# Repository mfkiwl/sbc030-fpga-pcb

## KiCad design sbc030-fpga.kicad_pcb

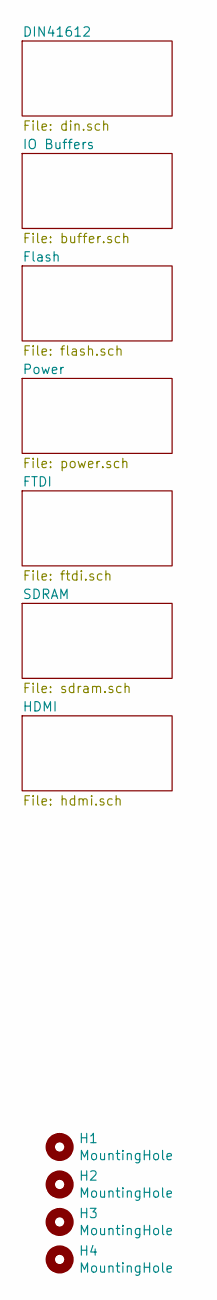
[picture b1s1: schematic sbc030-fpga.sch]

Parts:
H1, H2, H3, H4: MountingHole; MountingHole_3.2mm_M3

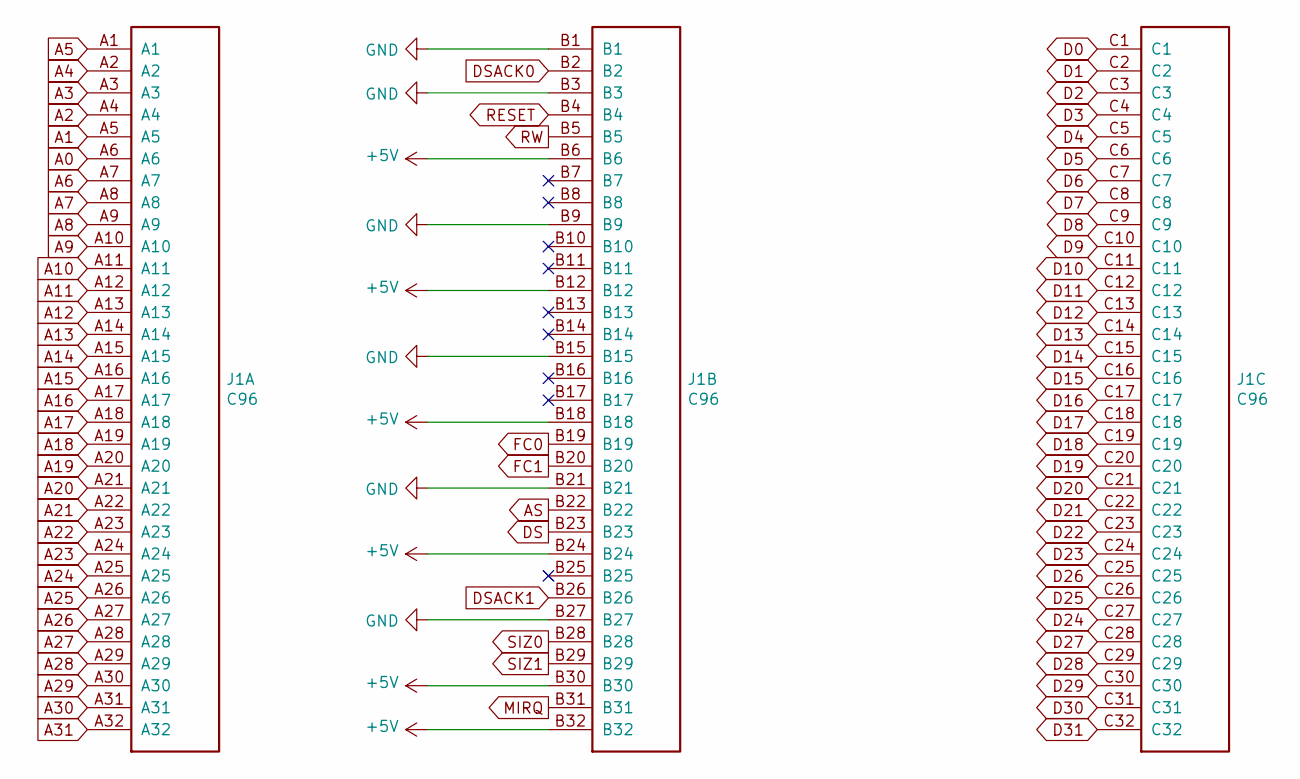
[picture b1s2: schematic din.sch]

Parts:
J1: C96; C96ABCM

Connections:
+5V: J1.B6, J1.B12, J1.B18, J1.B24, J1.B30, J1.B32; also elsewhere on the board
A0: J1.A6; also elsewhere on the board
A1: J1.A5; also elsewhere on the board
A2: J1.A4; also elsewhere on the board
A3: J1.A3; also elsewhere on the board
A4: J1.A2; also elsewhere on the board
A5: J1.A1; also elsewhere on the board
A6: J1.A7; also elsewhere on the board
A7: J1.A8; also elsewhere on the board
A8: J1.A9; also elsewhere on the board
A9: J1.A10; also elsewhere on the board
A10: J1.A11; also elsewhere on the board
A11: J1.A12; also elsewhere on the board
A12: J1.A13; also elsewhere on the board
A13: J1.A14; also elsewhere on the board
A14: J1.A15; also elsewhere on the board
A15: J1.A16; also elsewhere on the board
A16: J1.A17; also elsewhere on the board
A17: J1.A18; also elsewhere on the board
A18: J1.A19; also elsewhere on the board
A19: J1.A20; also elsewhere on the board
A20: J1.A21; also elsewhere on the board
A21: J1.A22; also elsewhere on the board
A22: J1.A23; also elsewhere on the board
A23: J1.A24; also elsewhere on the board
A24: J1.A25; also elsewhere on the board
A25: J1.A26; also elsewhere on the board
A26: J1.A27; also elsewhere on the board
A27: J1.A28; also elsewhere on the board
A28: J1.A29; also elsewhere on the board
A29: J1.A30; also elsewhere on the board
A30: J1.A31; also elsewhere on the board
A31: J1.A32; also elsewhere on the board
AS: J1.B22; also elsewhere on the board
D0: J1.C1; also elsewhere on the board
D1: J1.C2; also elsewhere on the board
D2: J1.C3; also elsewhere on the board
D3: J1.C4; also elsewhere on the board
D4: J1.C5; also elsewhere on the board
D5: J1.C6; also elsewhere on the board
D6: J1.C7; also elsewhere on the board
D7: J1.C8; also elsewhere on the board
D8: J1.C9; also elsewhere on the board
D9: J1.C10; also elsewhere on the board
D10: J1.C11; also elsewhere on the board
D11: J1.C12; also elsewhere on the board
D12: J1.C13; also elsewhere on the board
D13: J1.C14; also elsewhere on the board
D14: J1.C15; also elsewhere on the board
D15: J1.C16; also elsewhere on the board
D16: J1.C17; also elsewhere on the board
D17: J1.C18; also elsewhere on the board
D18: J1.C19; also elsewhere on the board
D19: J1.C20; also elsewhere on the board
D20: J1.C21; also elsewhere on the board
D21: J1.C22; also elsewhere on the board
D22: J1.C23; also elsewhere on the board
D23: J1.C24; also elsewhere on the board
D24: J1.C27; also elsewhere on the board
D25: J1.C26; also elsewhere on the board
D26: J1.C25; also elsewhere on the board
D27: J1.C28; also elsewhere on the board
D28: J1.C29; also elsewhere on the board
D29: J1.C30; also elsewhere on the board
D30: J1.C31; also elsewhere on the board
D31: J1.C32; also elsewhere on the board
DS: J1.B23; also elsewhere on the board
DSACK0: J1.B2; also elsewhere on the board
DSACK1: J1.B26; also elsewhere on the board
FC0: J1.B19; also elsewhere on the board
FC1: J1.B20; also elsewhere on the board
GND: J1.B1, J1.B3, J1.B9, J1.B15, J1.B21, J1.B27; also elsewhere on the board
MIRQ: J1.B31; also elsewhere on the board
RESET: J1.B4; also elsewhere on the board
RW: J1.B5; also elsewhere on the board
SIZ0: J1.B28; also elsewhere on the board
SIZ1: J1.B29; also elsewhere on the board

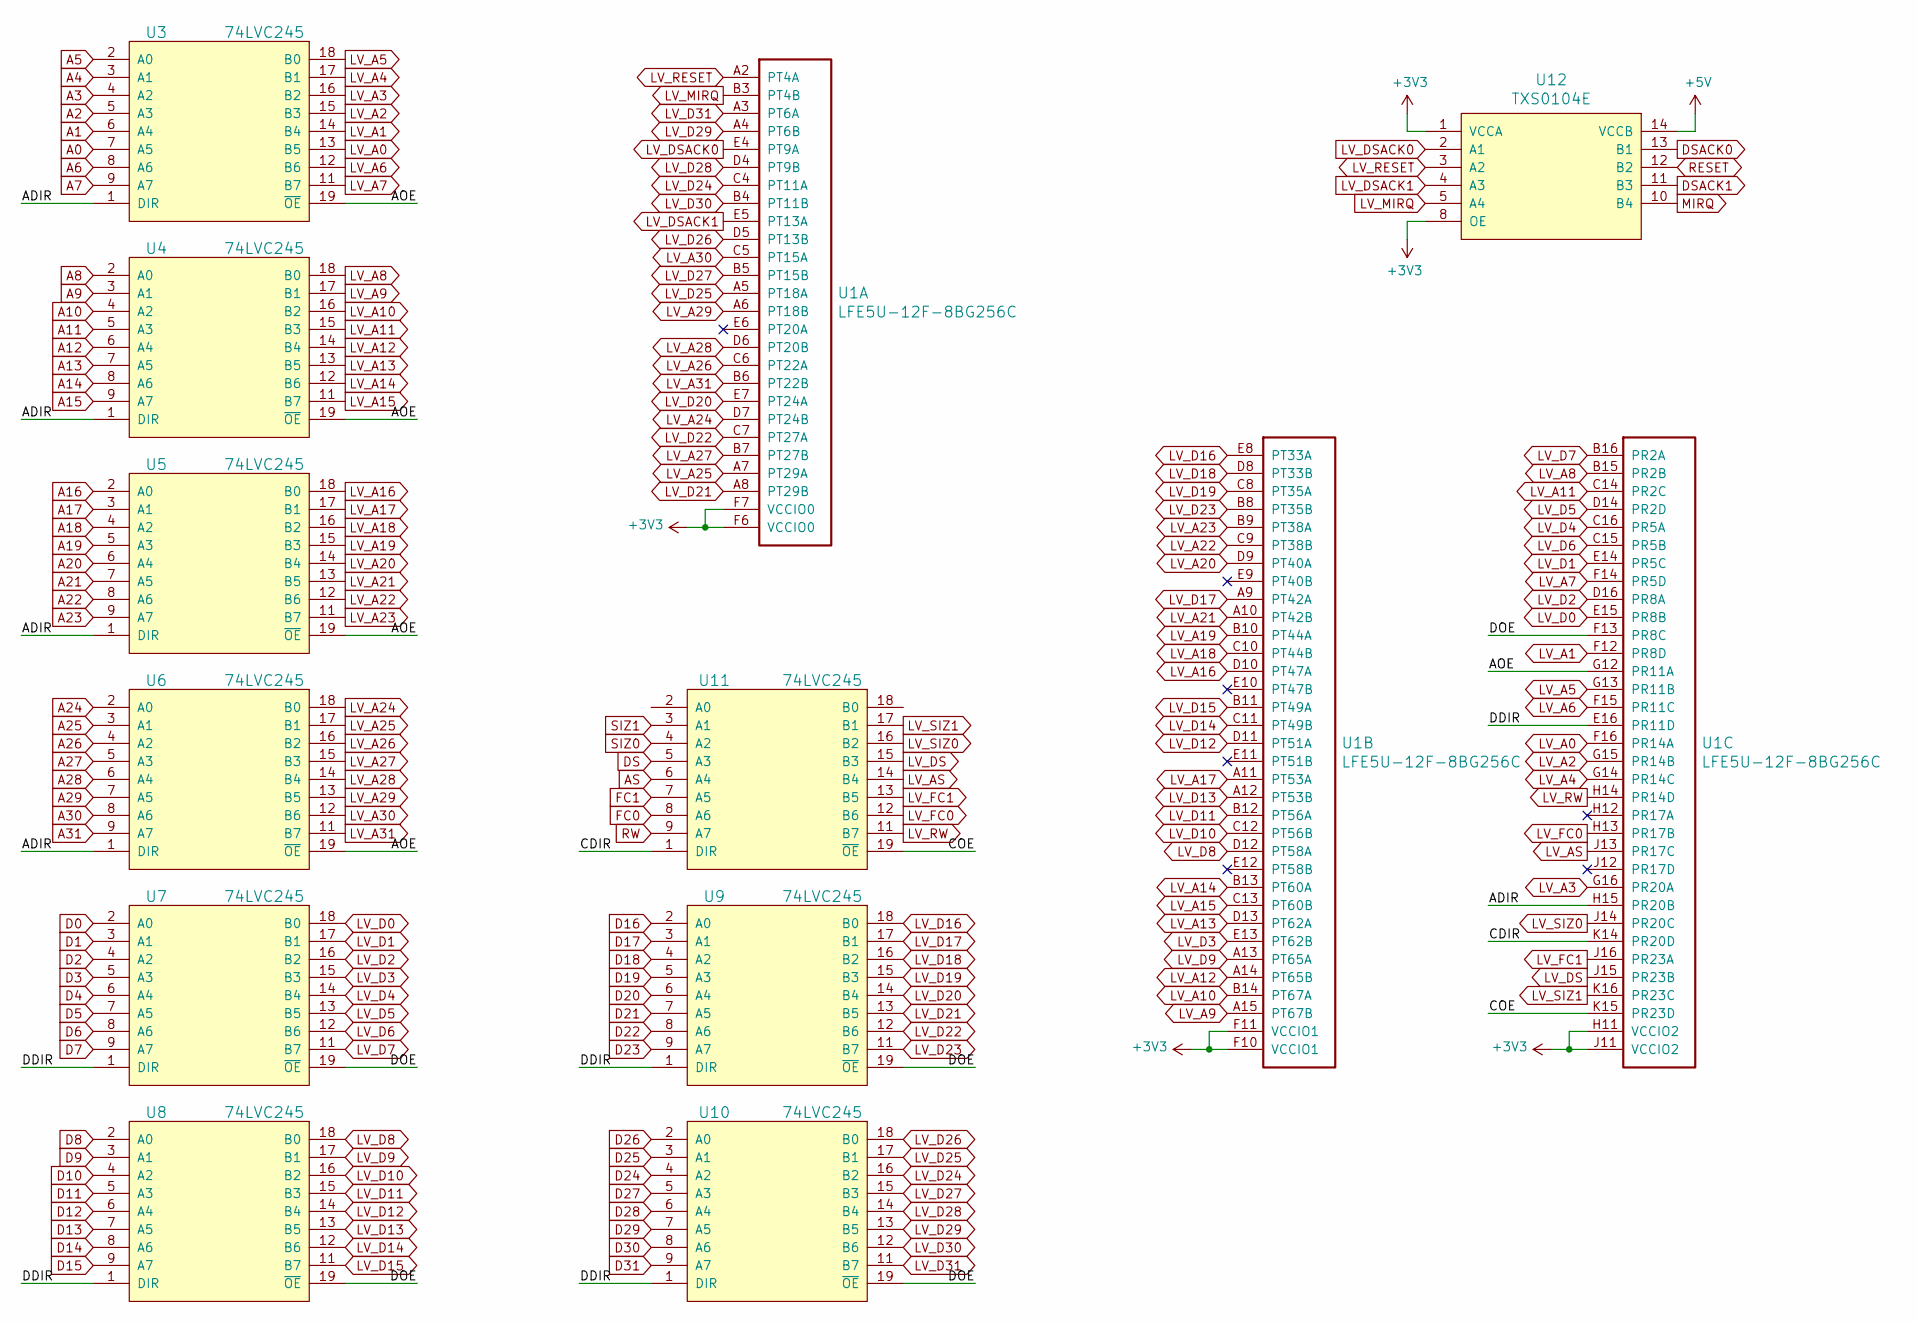
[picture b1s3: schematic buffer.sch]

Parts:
U1: LFE5U-12F-8BG256C; BGA-256_14.0x14.0mm_Layout16x16_P0.8mm_Ball0.45mm_Pad0.32mm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
U3, U4, U5, U6, U7, U8, U9, U10, U11: 74LVC245; TSSOP-20_4.4x6.5mm_P0.65mm
U12: TXS0104E; TSSOP-14_4.4x5mm_P0.65mm

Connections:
+3V3: U1.F6 (VCCIO0), U1.F7 (VCCIO0), U1.F10 (VCCIO1), U1.F11 (VCCIO1), U1.H11 (VCCIO2), U1.J11 (VCCIO2), U3.20 (VCC), U4.20 (VCC), U5.20 (VCC), U6.20 (VCC), U7.20 (VCC), U8.20 (VCC), U9.20 (VCC), U10.20 (VCC), U11.20 (VCC), U12.1 (VCCA), U12.8 (OE); also elsewhere on the board
+5V: U12.14 (VCCB); also elsewhere on the board
/IO Buffers/ADIR: U1.H15 (PR20B), U3.1 (DIR), U4.1 (DIR), U5.1 (DIR), U6.1 (DIR)
/IO Buffers/AOE: U1.G12 (PR11A), U3.19 (~OE), U4.19 (~OE), U5.19 (~OE), U6.19 (~OE)
/IO Buffers/CDIR: U1.K14 (PR20D), U11.1 (DIR)
/IO Buffers/COE: U1.K15 (PR23D), U11.19 (~OE)
/IO Buffers/DDIR: U1.E16 (PR11D), U7.1 (DIR), U8.1 (DIR), U9.1 (DIR), U10.1 (DIR)
/IO Buffers/DOE: U1.F13 (PR8C), U7.19 (~OE), U8.19 (~OE), U9.19 (~OE), U10.19 (~OE)
A0: U3.7 (A5); also elsewhere on the board
A1: U3.6 (A4); also elsewhere on the board
A2: U3.5 (A3); also elsewhere on the board
A3: U3.4 (A2); also elsewhere on the board
A4: U3.3 (A1); also elsewhere on the board
A5: U3.2 (A0); also elsewhere on the board
A6: U3.8 (A6); also elsewhere on the board
A7: U3.9 (A7); also elsewhere on the board
A8: U4.2 (A0); also elsewhere on the board
A9: U4.3 (A1); also elsewhere on the board
A10: U4.4 (A2); also elsewhere on the board
A11: U4.5 (A3); also elsewhere on the board
A12: U4.6 (A4); also elsewhere on the board
A13: U4.7 (A5); also elsewhere on the board
A14: U4.8 (A6); also elsewhere on the board
A15: U4.9 (A7); also elsewhere on the board
A16: U5.2 (A0); also elsewhere on the board
A17: U5.3 (A1); also elsewhere on the board
A18: U5.4 (A2); also elsewhere on the board
A19: U5.5 (A3); also elsewhere on the board
A20: U5.6 (A4); also elsewhere on the board
A21: U5.7 (A5); also elsewhere on the board
A22: U5.8 (A6); also elsewhere on the board
A23: U5.9 (A7); also elsewhere on the board
A24: U6.2 (A0); also elsewhere on the board
A25: U6.3 (A1); also elsewhere on the board
A26: U6.4 (A2); also elsewhere on the board
A27: U6.5 (A3); also elsewhere on the board
A28: U6.6 (A4); also elsewhere on the board
A29: U6.7 (A5); also elsewhere on the board
A30: U6.8 (A6); also elsewhere on the board
A31: U6.9 (A7); also elsewhere on the board
AS: U11.6 (A4); also elsewhere on the board
D0: U7.2 (A0); also elsewhere on the board
D1: U7.3 (A1); also elsewhere on the board
D2: U7.4 (A2); also elsewhere on the board
D3: U7.5 (A3); also elsewhere on the board
D4: U7.6 (A4); also elsewhere on the board
D5: U7.7 (A5); also elsewhere on the board
D6: U7.8 (A6); also elsewhere on the board
D7: U7.9 (A7); also elsewhere on the board
D8: U8.2 (A0); also elsewhere on the board
D9: U8.3 (A1); also elsewhere on the board
D10: U8.4 (A2); also elsewhere on the board
D11: U8.5 (A3); also elsewhere on the board
D12: U8.6 (A4); also elsewhere on the board
D13: U8.7 (A5); also elsewhere on the board
D14: U8.8 (A6); also elsewhere on the board
D15: U8.9 (A7); also elsewhere on the board
D16: U9.2 (A0); also elsewhere on the board
D17: U9.3 (A1); also elsewhere on the board
D18: U9.4 (A2); also elsewhere on the board
D19: U9.5 (A3); also elsewhere on the board
D20: U9.6 (A4); also elsewhere on the board
D21: U9.7 (A5); also elsewhere on the board
D22: U9.8 (A6); also elsewhere on the board
D23: U9.9 (A7); also elsewhere on the board
D24: U10.4 (A2); also elsewhere on the board
D25: U10.3 (A1); also elsewhere on the board
D26: U10.2 (A0); also elsewhere on the board
D27: U10.5 (A3); also elsewhere on the board
D28: U10.6 (A4); also elsewhere on the board
D29: U10.7 (A5); also elsewhere on the board
D30: U10.8 (A6); also elsewhere on the board
D31: U10.9 (A7); also elsewhere on the board
DS: U11.5 (A3); also elsewhere on the board
DSACK0: U12.13 (B1); also elsewhere on the board
DSACK1: U12.11 (B3); also elsewhere on the board
FC0: U11.8 (A6); also elsewhere on the board
FC1: U11.7 (A5); also elsewhere on the board
GND: U3.10 (GND), U4.10 (GND), U5.10 (GND), U6.10 (GND), U7.10 (GND), U8.10 (GND), U9.10 (GND), U10.10 (GND), U11.10 (GND), U12.7 (GND); also elsewhere on the board
LV_A0: U1.F16 (PR14A), U3.13 (B5)
LV_A1: U1.F12 (PR8D), U3.14 (B4)
LV_A2: U1.G15 (PR14B), U3.15 (B3)
LV_A3: U1.G16 (PR20A), U3.16 (B2)
LV_A4: U1.G14 (PR14C), U3.17 (B1)
LV_A5: U1.G13 (PR11B), U3.18 (B0)
LV_A6: U1.F15 (PR11C), U3.12 (B6)
LV_A7: U1.F14 (PR5D), U3.11 (B7)
LV_A8: U1.B15 (PR2B), U4.18 (B0)
LV_A9: U1.A15 (PT67B), U4.17 (B1)
LV_A10: U1.B14 (PT67A), U4.16 (B2)
LV_A11: U1.C14 (PR2C), U4.15 (B3)
LV_A12: U1.A14 (PT65B), U4.14 (B4)
LV_A13: U1.D13 (PT62A), U4.13 (B5)
LV_A14: U1.B13 (PT60A), U4.12 (B6)
LV_A15: U1.C13 (PT60B), U4.11 (B7)
LV_A16: U1.D10 (PT47A), U5.18 (B0)
LV_A17: U1.A11 (PT53A), U5.17 (B1)
LV_A18: U1.C10 (PT44B), U5.16 (B2)
LV_A19: U1.B10 (PT44A), U5.15 (B3)
LV_A20: U1.D9 (PT40A), U5.14 (B4)
LV_A21: U1.A10 (PT42B), U5.13 (B5)
LV_A22: U1.C9 (PT38B), U5.12 (B6)
LV_A23: U1.B9 (PT38A), U5.11 (B7)
LV_A24: U1.D7 (PT24B), U6.18 (B0)
LV_A25: U1.A7 (PT29A), U6.17 (B1)
LV_A26: U1.C6 (PT22A), U6.16 (B2)
LV_A27: U1.B7 (PT27B), U6.15 (B3)
LV_A28: U1.D6 (PT20B), U6.14 (B4)
LV_A29: U1.A6 (PT18B), U6.13 (B5)
LV_A30: U1.C5 (PT15A), U6.12 (B6)
LV_A31: U1.B6 (PT22B), U6.11 (B7)
LV_AS: U1.J13 (PR17C), U11.14 (B4)
LV_D0: U1.E15 (PR8B), U7.18 (B0)
LV_D1: U1.E14 (PR5C), U7.17 (B1)
LV_D2: U1.D16 (PR8A), U7.16 (B2)
LV_D3: U1.E13 (PT62B), U7.15 (B3)
LV_D4: U1.C16 (PR5A), U7.14 (B4)
LV_D5: U1.D14 (PR2D), U7.13 (B5)
LV_D6: U1.C15 (PR5B), U7.12 (B6)
LV_D7: U1.B16 (PR2A), U7.11 (B7)
LV_D8: U1.D12 (PT58A), U8.18 (B0)
LV_D9: U1.A13 (PT65A), U8.17 (B1)
LV_D10: U1.C12 (PT56B), U8.16 (B2)
LV_D11: U1.B12 (PT56A), U8.15 (B3)
LV_D12: U1.D11 (PT51A), U8.14 (B4)
LV_D13: U1.A12 (PT53B), U8.13 (B5)
LV_D14: U1.C11 (PT49B), U8.12 (B6)
LV_D15: U1.B11 (PT49A), U8.11 (B7)
LV_D16: U1.E8 (PT33A), U9.18 (B0)
LV_D17: U1.A9 (PT42A), U9.17 (B1)
LV_D18: U1.D8 (PT33B), U9.16 (B2)
LV_D19: U1.C8 (PT35A), U9.15 (B3)
LV_D20: U1.E7 (PT24A), U9.14 (B4)
LV_D21: U1.A8 (PT29B), U9.13 (B5)
LV_D22: U1.C7 (PT27A), U9.12 (B6)
LV_D23: U1.B8 (PT35B), U9.11 (B7)
LV_D24: U1.C4 (PT11A), U10.16 (B2)
LV_D25: U1.A5 (PT18A), U10.17 (B1)
LV_D26: U1.D5 (PT13B), U10.18 (B0)
LV_D27: U1.B5 (PT15B), U10.15 (B3)
LV_D28: U1.D4 (PT9B), U10.14 (B4)
LV_D29: U1.A4 (PT6B), U10.13 (B5)
LV_D30: U1.B4 (PT11B), U10.12 (B6)
LV_D31: U1.A3 (PT6A), U10.11 (B7)
LV_DS: U1.J15 (PR23B), U11.15 (B3)
LV_DSACK0: U1.E4 (PT9A), U12.2 (A1)
LV_DSACK1: U1.E5 (PT13A), U12.4 (A3)
LV_FC0: U1.H13 (PR17B), U11.12 (B6)
LV_FC1: U1.J16 (PR23A), U11.13 (B5)
LV_MIRQ: U1.B3 (PT4B), U12.5 (A4)
LV_RESET: U1.A2 (PT4A), U12.3 (A2)
LV_RW: U1.H14 (PR14D), U11.11 (B7)
LV_SIZ0: U1.J14 (PR20C), U11.16 (B2)
LV_SIZ1: U1.K16 (PR23C), U11.17 (B1)
MIRQ: U12.10 (B4); also elsewhere on the board
RESET: U12.12 (B2); also elsewhere on the board
RW: U11.9 (A7); also elsewhere on the board
SIZ0: U11.4 (A2); also elsewhere on the board
SIZ1: U11.3 (A1); also elsewhere on the board

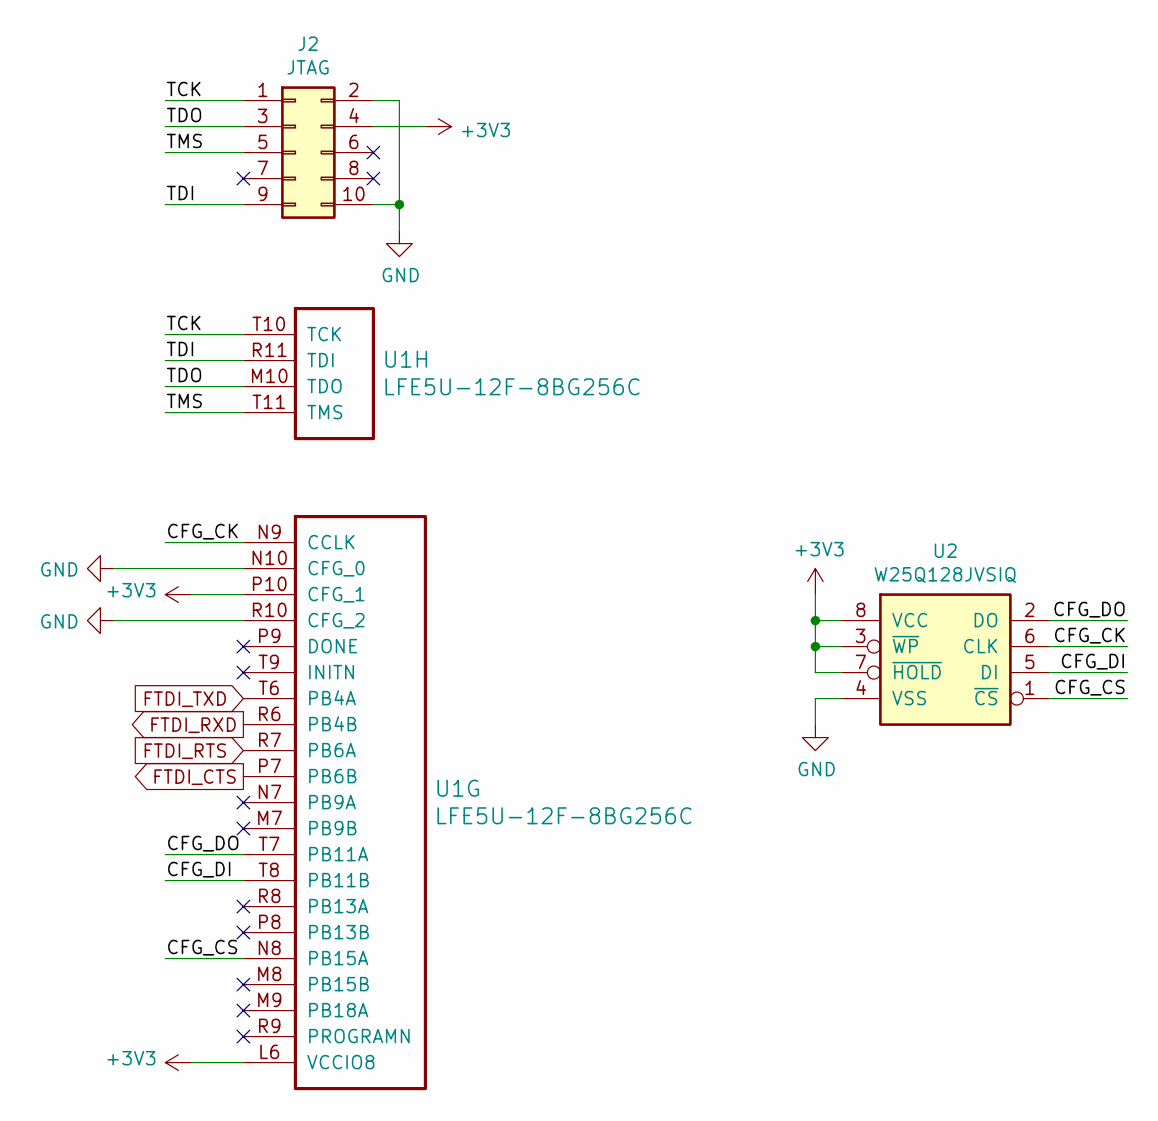
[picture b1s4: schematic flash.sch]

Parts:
J2: JTAG; PinHeader_2x05_P2.54mm_Vertical
U1: LFE5U-12F-8BG256C; BGA-256_14.0x14.0mm_Layout16x16_P0.8mm_Ball0.45mm_Pad0.32mm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
U2: W25Q128JVSIQ; SOIJ-8_5.3x5.3mm_P1.27mm

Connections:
+3V3: J2.4, U1.L6 (VCCIO8), U1.P10 (CFG_1), U2.3 (~WP), U2.7 (~HOLD), U2.8 (VCC); also elsewhere on the board
/Flash/CFG_CK: U1.N9 (CCLK), U2.6 (CLK)
/Flash/CFG_CS: U1.N8 (PB15A), U2.1 (~CS)
/Flash/CFG_DI: U1.T8 (PB11B), U2.5 (DI)
/Flash/CFG_DO: U1.T7 (PB11A), U2.2 (DO)
/Flash/TCK: J2.1, U1.T10 (TCK)
/Flash/TDI: J2.9, U1.R11 (TDI)
/Flash/TDO: J2.3, U1.M10 (TDO)
/Flash/TMS: J2.5, U1.T11 (TMS)
FTDI_CTS: U1.P7 (PB6B); also elsewhere on the board
FTDI_RTS: U1.R7 (PB6A); also elsewhere on the board
FTDI_RXD: U1.R6 (PB4B); also elsewhere on the board
FTDI_TXD: U1.T6 (PB4A); also elsewhere on the board
GND: J2.2, J2.10, U1.N10 (CFG_0), U1.R10 (CFG_2), U2.4 (VSS); also elsewhere on the board

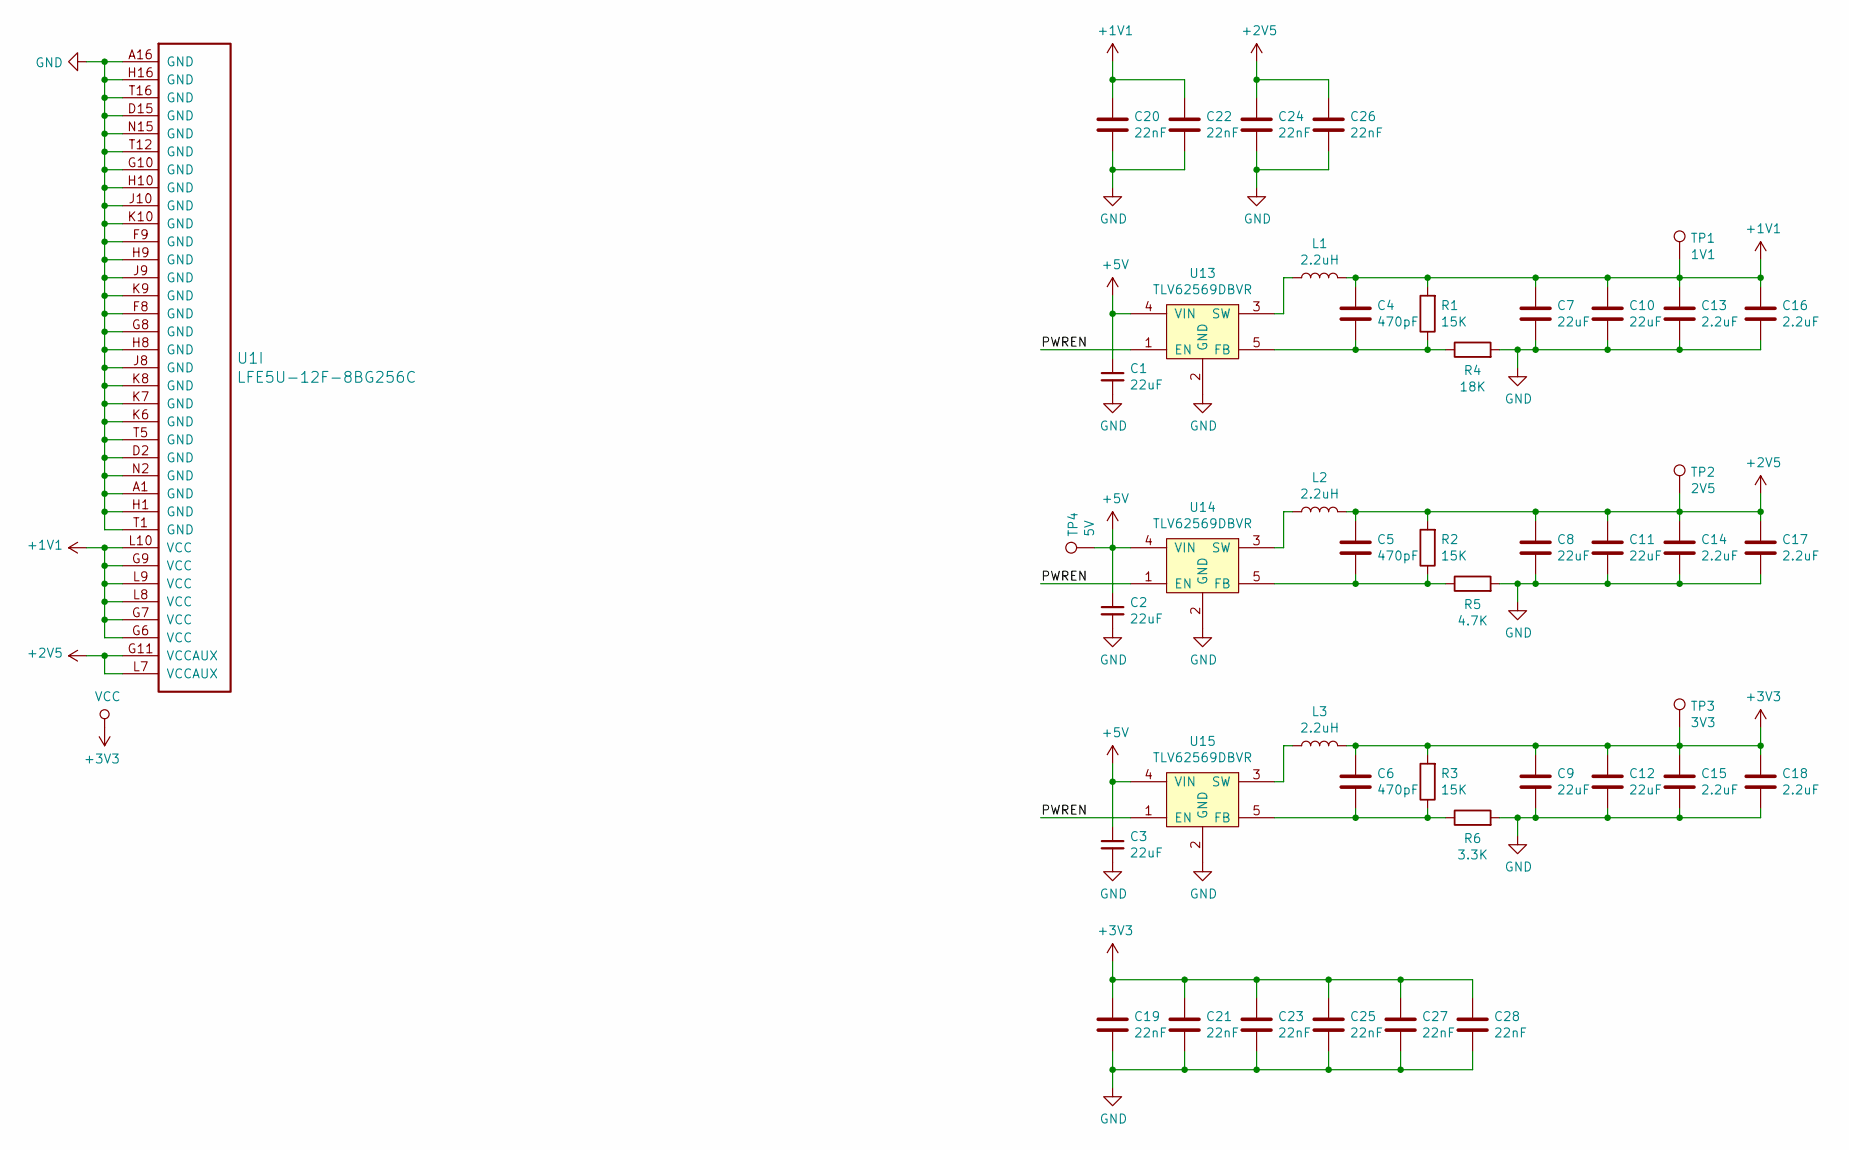
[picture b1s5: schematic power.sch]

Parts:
C1, C2, C3, C7, C8, C9, C10, C11, C12: 22uF; C_0805_2012Metric
C4, C5, C6: 470pF; C_0603_1608Metric
C13, C14, C15, C16, C17, C18: 2.2uF; C_0603_1608Metric
C19, C20, C21, C22, C23, C24, C25, C26, C27, C28: 22nF; C_0402_1005Metric
L1, L2, L3: 2.2uH; L_1210_3225Metric
R1, R2, R3: 15K; R_0603_1608Metric
R4: 18K; R_0603_1608Metric
R5: 4.7K; R_0603_1608Metric
R6: 3.3K; R_0603_1608Metric
TP1: 1V1; TestPoint_Pad_D1.0mm
TP2: 2V5; TestPoint_Pad_D1.0mm
TP3: 3V3; TestPoint_Pad_D1.0mm
TP4: 5V; TestPoint_Pad_D1.0mm
U1: LFE5U-12F-8BG256C; BGA-256_14.0x14.0mm_Layout16x16_P0.8mm_Ball0.45mm_Pad0.32mm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
U13, U14, U15: TLV62569DBVR; SOT-23-5

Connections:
+1V1: C4.1, C7.1, C10.1, C13.1, C16.1, C20.1, C22.1, L1.2, R1.2, TP1.1, U1.G6 (VCC), U1.G7 (VCC), U1.G9 (VCC), U1.L8 (VCC), U1.L9 (VCC), U1.L10 (VCC)
+2V5: C5.1, C8.1, C11.1, C14.1, C17.1, C24.1, C26.1, L2.2, R2.2, TP2.1, U1.G11 (VCCAUX), U1.L7 (VCCAUX)
+3V3: C6.1, C9.1, C12.1, C15.1, C18.1, C19.1, C21.1, C23.1, C25.1, C27.1, C28.1, L3.2, R3.2, TP3.1; also elsewhere on the board
+5V: C1.1, C2.1, C3.1, TP4.1, U13.4 (VIN), U14.4 (VIN), U15.4 (VIN); also elsewhere on the board
/Power/PWREN: U13.1 (EN), U14.1 (EN), U15.1 (EN)
GND: C1.2, C2.2, C3.2, C7.2, C8.2, C9.2, C10.2, C11.2, C12.2, C13.2, C14.2, C15.2, C16.2, C17.2, C18.2, C19.2, C20.2, C21.2, C22.2, C23.2, C24.2, C25.2, C26.2, C27.2, C28.2, R4.2, R5.2, R6.2, U1.A1 (GND), U1.A16 (GND), U1.D2 (GND), U1.D15 (GND), U1.F8 (GND), U1.F9 (GND), U1.G8 (GND), U1.G10 (GND), U1.H1 (GND), U1.H8 (GND), U1.H9 (GND), U1.H10 (GND), U1.H16 (GND), U1.J8 (GND), U1.J9 (GND), U1.J10 (GND), U1.K6 (GND), U1.K7 (GND), U1.K8 (GND), U1.K9 (GND), U1.K10 (GND), U1.N2 (GND), U1.N15 (GND), U1.T1 (GND), U1.T5 (GND), U1.T12 (GND), U1.T16 (GND), U13.2 (GND), U14.2 (GND), U15.2 (GND); also elsewhere on the board
unnamed: C4.2, R1.1, R4.1, U13.5 (FB)
unnamed: C5.2, R2.1, R5.1, U14.5 (FB)
unnamed: C6.2, R3.1, R6.1, U15.5 (FB)
unnamed: L1.1, U13.3 (SW)
unnamed: L2.1, U14.3 (SW)
unnamed: L3.1, U15.3 (SW)

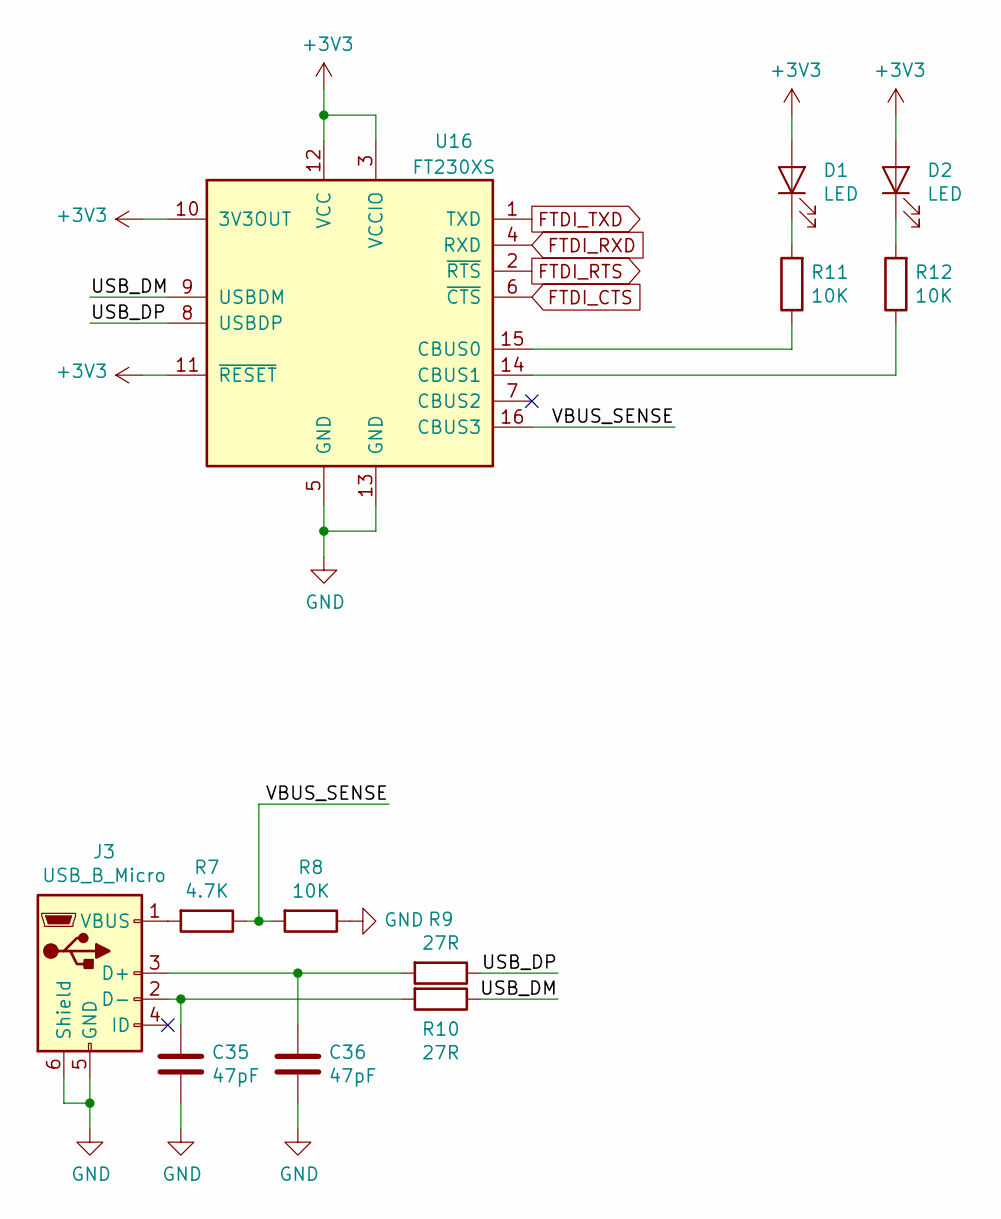
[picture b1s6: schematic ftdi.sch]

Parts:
C35, C36: 47pF; C_0603_1608Metric
D1, D2: LED; LED_1206_3216Metric
J3: USB_B_Micro; USB_Micro-B_GCT_USB3076-30-A
R7: 4.7K; R_0805_2012Metric
R8, R11, R12: 10K; R_0805_2012Metric
R9, R10: 27R; R_0805_2012Metric
U16: FT230XS; SSOP-16_3.9x4.9mm_P0.635mm

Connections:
+3V3: D1.2 (A), D2.2 (A), U16.3 (VCCIO), U16.10 (3V3OUT), U16.11 (~RESET), U16.12 (VCC); also elsewhere on the board
/FTDI/USB_DM: R10.1, U16.9 (USBDM)
/FTDI/USB_DP: R9.1, U16.8 (USBDP)
/FTDI/VBUS_SENSE: R7.1, R8.2, U16.16 (CBUS3)
FTDI_CTS: U16.6 (~CTS); also elsewhere on the board
FTDI_RTS: U16.2 (~RTS); also elsewhere on the board
FTDI_RXD: U16.4 (RXD); also elsewhere on the board
FTDI_TXD: U16.1 (TXD); also elsewhere on the board
GND: C35.1, C36.1, J3.5 (GND), J3.6 (Shield), R8.1, U16.5 (GND), U16.13 (GND); also elsewhere on the board
unnamed: C35.2, J3.2 (D-), R10.2
unnamed: C36.2, J3.3 (D+), R9.2
unnamed: D1.1 (K), R11.2
unnamed: D2.1 (K), R12.2
unnamed: J3.1 (VBUS), R7.2
unnamed: R11.1, U16.15 (CBUS0)
unnamed: R12.1, U16.14 (CBUS1)

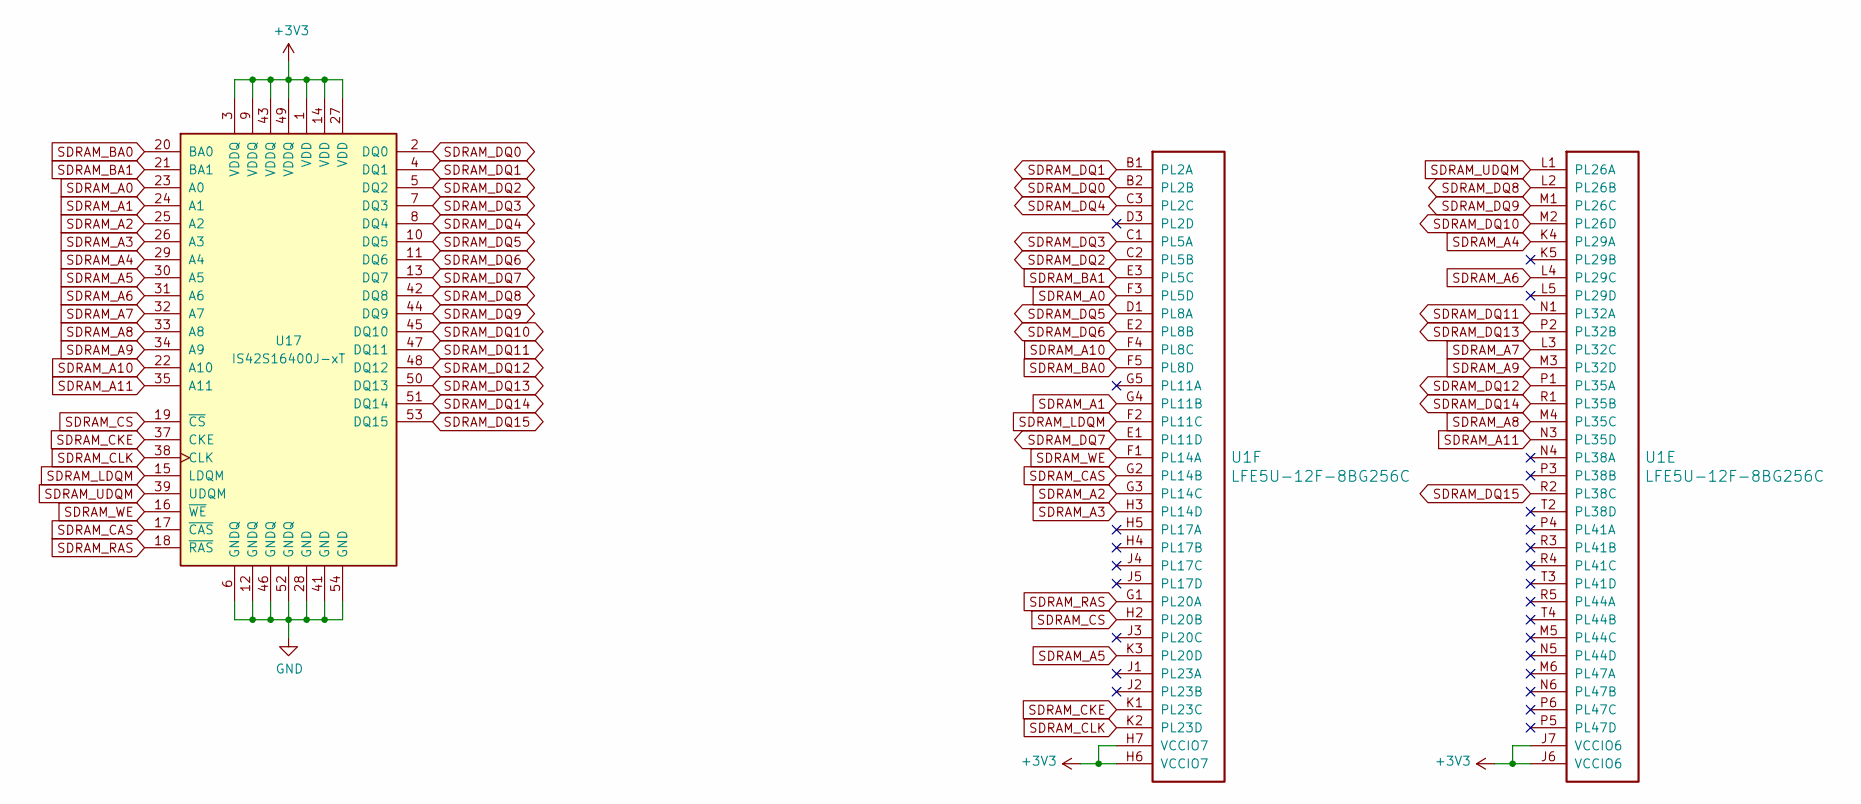
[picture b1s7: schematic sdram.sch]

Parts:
U1: LFE5U-12F-8BG256C; BGA-256_14.0x14.0mm_Layout16x16_P0.8mm_Ball0.45mm_Pad0.32mm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
U17: IS42S16400J-xT; TSOP-II-54_22.2x10.16mm_P0.8mm

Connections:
+3V3: U1.H6 (VCCIO7), U1.H7 (VCCIO7), U1.J6 (VCCIO6), U1.J7 (VCCIO6), U17.1 (VDD), U17.3 (VDDQ), U17.9 (VDDQ), U17.14 (VDD), U17.27 (VDD), U17.43 (VDDQ), U17.49 (VDDQ); also elsewhere on the board
GND: U17.6 (GNDQ), U17.12 (GNDQ), U17.28 (GND), U17.41 (GND), U17.46 (GNDQ), U17.52 (GNDQ), U17.54 (GND); also elsewhere on the board
SDRAM_A0: U1.F3 (PL5D), U17.23 (A0)
SDRAM_A1: U1.G4 (PL11B), U17.24 (A1)
SDRAM_A2: U1.G3 (PL14C), U17.25 (A2)
SDRAM_A3: U1.H3 (PL14D), U17.26 (A3)
SDRAM_A4: U1.K4 (PL29A), U17.29 (A4)
SDRAM_A5: U1.K3 (PL20D), U17.30 (A5)
SDRAM_A6: U1.L4 (PL29C), U17.31 (A6)
SDRAM_A7: U1.L3 (PL32C), U17.32 (A7)
SDRAM_A8: U1.M4 (PL35C), U17.33 (A8)
SDRAM_A9: U1.M3 (PL32D), U17.34 (A9)
SDRAM_A10: U1.F4 (PL8C), U17.22 (A10)
SDRAM_A11: U1.N3 (PL35D), U17.35 (A11)
SDRAM_BA0: U1.F5 (PL8D), U17.20 (BA0)
SDRAM_BA1: U1.E3 (PL5C), U17.21 (BA1)
SDRAM_CAS: U1.G2 (PL14B), U17.17 (~CAS)
SDRAM_CKE: U1.K1 (PL23C), U17.37 (CKE)
SDRAM_CLK: U1.K2 (PL23D), U17.38 (CLK)
SDRAM_CS: U1.H2 (PL20B), U17.19 (~CS)
SDRAM_DQ0: U1.B2 (PL2B), U17.2 (DQ0)
SDRAM_DQ1: U1.B1 (PL2A), U17.4 (DQ1)
SDRAM_DQ2: U1.C2 (PL5B), U17.5 (DQ2)
SDRAM_DQ3: U1.C1 (PL5A), U17.7 (DQ3)
SDRAM_DQ4: U1.C3 (PL2C), U17.8 (DQ4)
SDRAM_DQ5: U1.D1 (PL8A), U17.10 (DQ5)
SDRAM_DQ6: U1.E2 (PL8B), U17.11 (DQ6)
SDRAM_DQ7: U1.E1 (PL11D), U17.13 (DQ7)
SDRAM_DQ8: U1.L2 (PL26B), U17.42 (DQ8)
SDRAM_DQ9: U1.M1 (PL26C), U17.44 (DQ9)
SDRAM_DQ10: U1.M2 (PL26D), U17.45 (DQ10)
SDRAM_DQ11: U1.N1 (PL32A), U17.47 (DQ11)
SDRAM_DQ12: U1.P1 (PL35A), U17.48 (DQ12)
SDRAM_DQ13: U1.P2 (PL32B), U17.50 (DQ13)
SDRAM_DQ14: U1.R1 (PL35B), U17.51 (DQ14)
SDRAM_DQ15: U1.R2 (PL38C), U17.53 (DQ15)
SDRAM_LDQM: U1.F2 (PL11C), U17.15 (LDQM)
SDRAM_RAS: U1.G1 (PL20A), U17.18 (~RAS)
SDRAM_UDQM: U1.L1 (PL26A), U17.39 (UDQM)
SDRAM_WE: U1.F1 (PL14A), U17.16 (~WE)

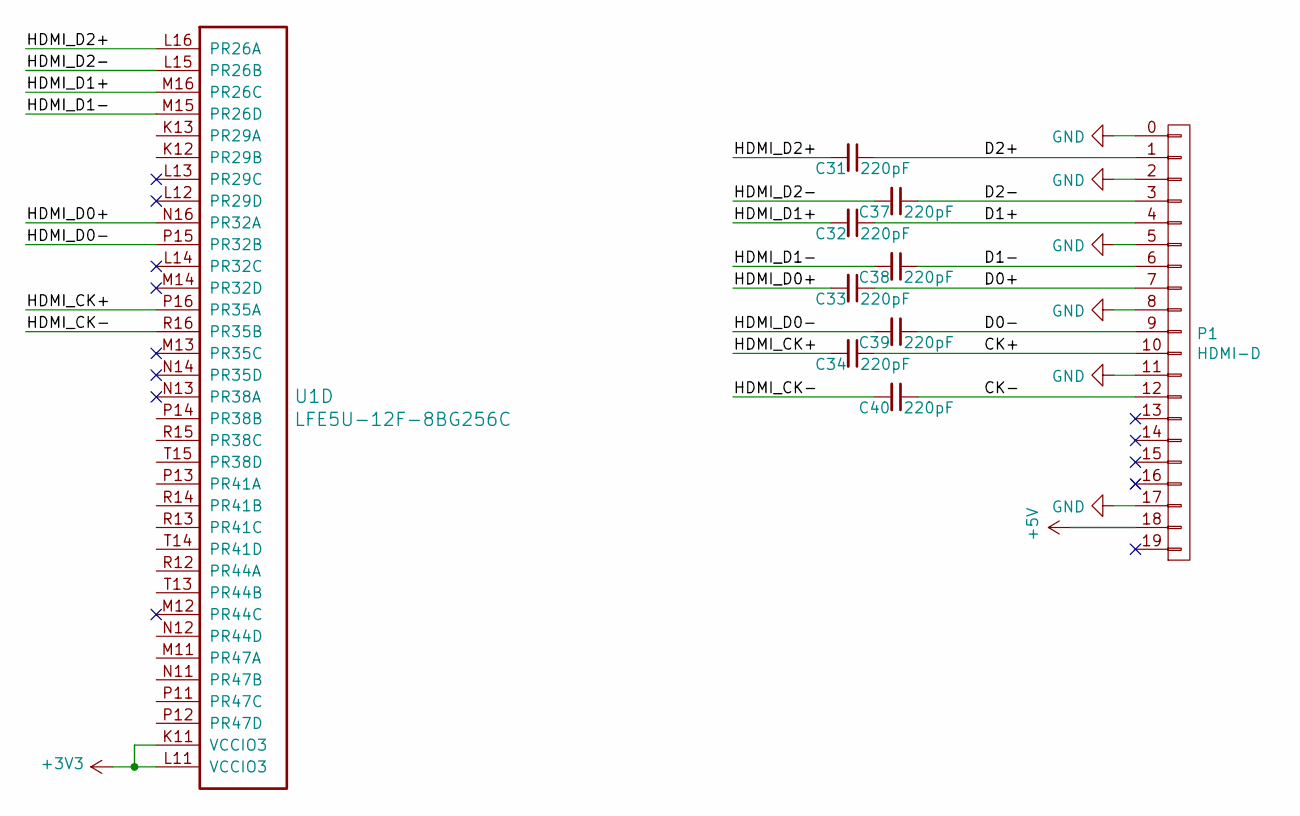
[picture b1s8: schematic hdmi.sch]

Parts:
C31, C32, C33, C34, C37, C38, C39, C40: 220pF; C_0603_1608Metric
P1: HDMI-D
U1: LFE5U-12F-8BG256C; BGA-256_14.0x14.0mm_Layout16x16_P0.8mm_Ball0.45mm_Pad0.32mm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

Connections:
+3V3: U1.K11 (VCCIO3), U1.L11 (VCCIO3); also elsewhere on the board
+5V: P1.18; also elsewhere on the board
/HDMI/CK+: C34.1, P1.10
/HDMI/CK-: C40.1, P1.12
/HDMI/D0+: C33.1, P1.7
/HDMI/D0-: C39.1, P1.9
/HDMI/D1+: C32.1, P1.4
/HDMI/D1-: C38.1, P1.6
/HDMI/D2+: C31.1, P1.1
/HDMI/D2-: C37.1, P1.3
/HDMI/HDMI_CK+: C34.2, U1.P16 (PR35A)
/HDMI/HDMI_CK-: C40.2, U1.R16 (PR35B)
/HDMI/HDMI_D0+: C33.2, U1.N16 (PR32A)
/HDMI/HDMI_D0-: C39.2, U1.P15 (PR32B)
/HDMI/HDMI_D1+: C32.2, U1.M16 (PR26C)
/HDMI/HDMI_D1-: C38.2, U1.M15 (PR26D)
/HDMI/HDMI_D2+: C31.2, U1.L16 (PR26A)
/HDMI/HDMI_D2-: C37.2, U1.L15 (PR26B)
GND: P1.0, P1.2, P1.5, P1.8, P1.11, P1.17; also elsewhere on the board
